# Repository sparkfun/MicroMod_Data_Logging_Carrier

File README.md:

SparkFun MicroMod Data Logging Carrier Board
========================================

[SparkFun MicroMod Data Logging Carrier Board (DEV-16829)](https://www.sparkfun.com/products/16829)

The SparkFun MicroMod Data Logging Carrier Board offers a highly customizable, low-power data logging platform using the MicroMod system allowing you to choose your own Processor Board to pair with the Carrier Board. The board features several connections for data collection including I<sup>2</sup>C, SPI and Serial UART.

Repository Contents
-------------------

* **/Examples** - Arduino example sketches
* **/Hardware** - Eagle design files (.brd, .sch)

Documentation
--------------
* **[Hookup Guide](https://learn.sparkfun.com/tutorials/micromod-data-logging-carrier-board-hookup-guide)** - Basic hookup guide for the SparkFun MicroMod Data Logging Carrier Board
* **[MicroMod Info Page](https://ww.sparkfun.com/micromod)** - MicroMod Information Page

Version History
---------------
* **[DEV-16829](https://www.sparkfun.com/products/16829)** - Initial release.

License Information
-------------------

This product is _**open source**_! 

Please review the LICENSE.md file for license information. 

If you have any questions or concerns on licensing, please contact technical support on our [SparkFun forums](https://forum.sparkfun.com/viewforum.php?f=152).

Distributed as-is; no warranty is given.

- Your friends at SparkFun.

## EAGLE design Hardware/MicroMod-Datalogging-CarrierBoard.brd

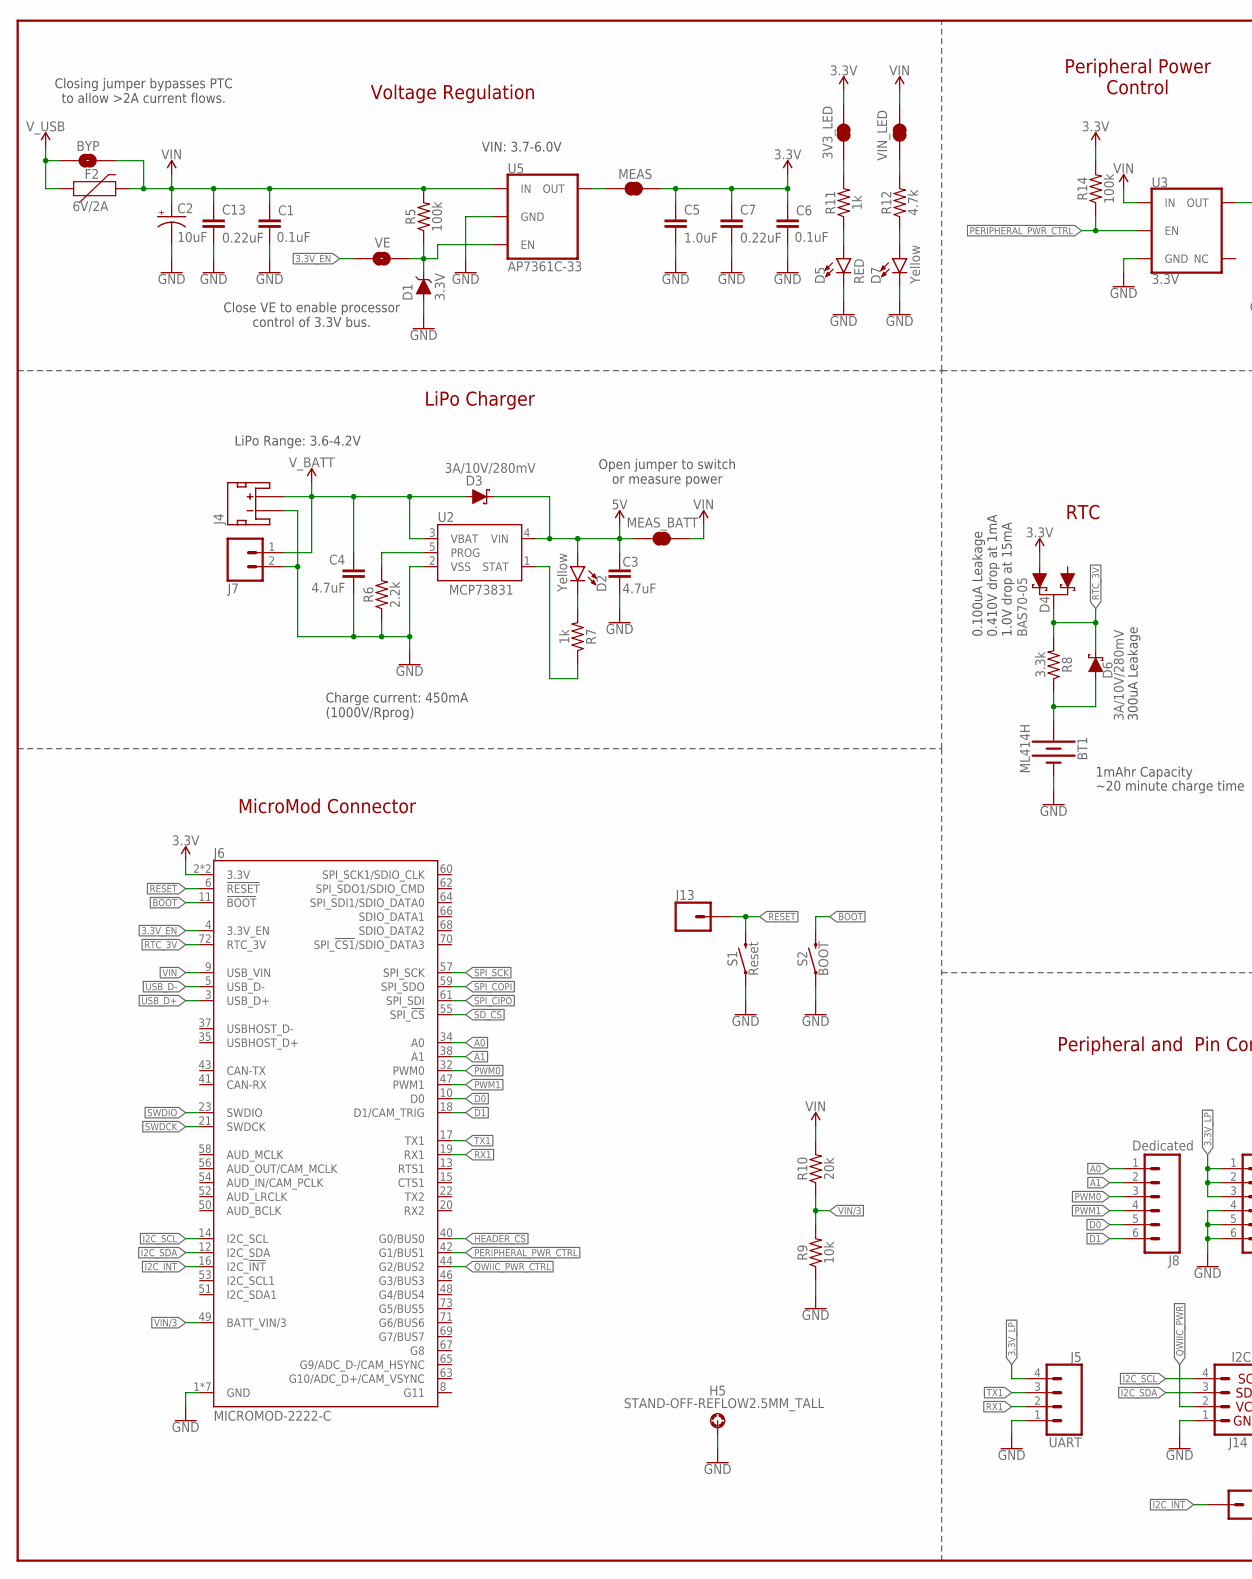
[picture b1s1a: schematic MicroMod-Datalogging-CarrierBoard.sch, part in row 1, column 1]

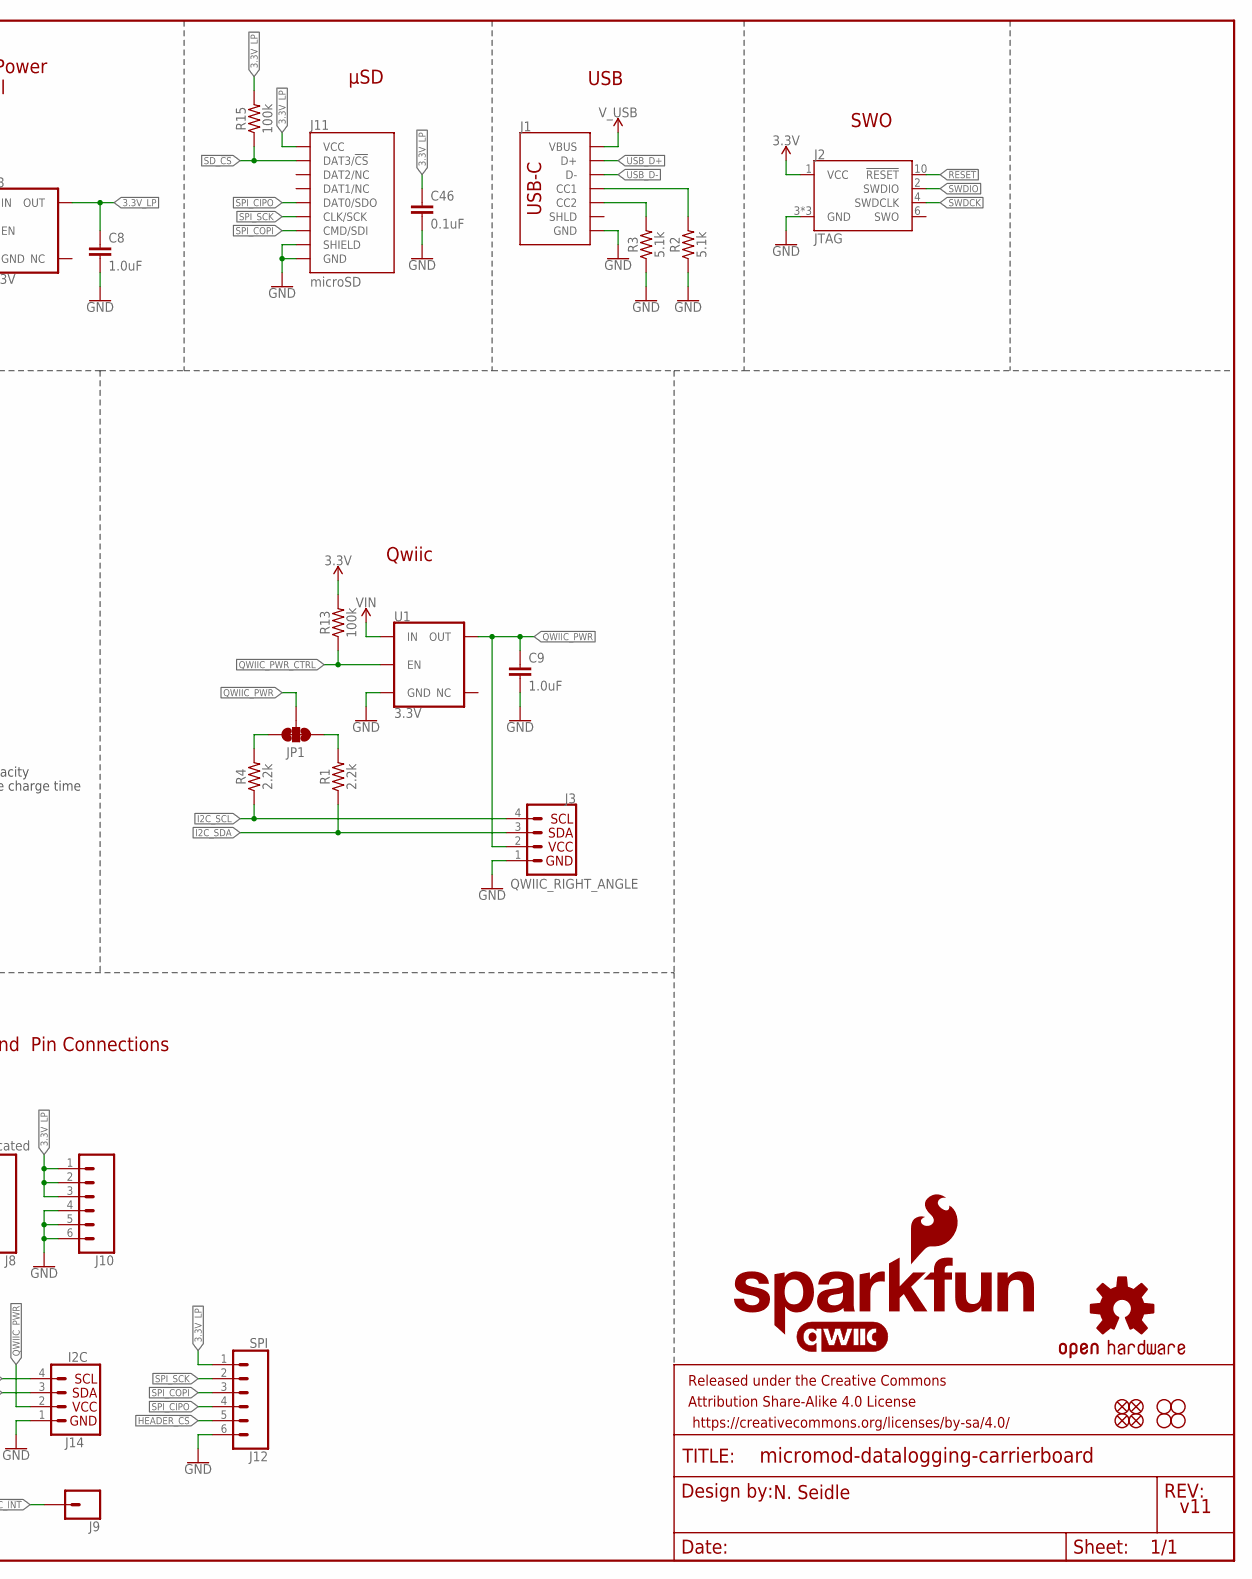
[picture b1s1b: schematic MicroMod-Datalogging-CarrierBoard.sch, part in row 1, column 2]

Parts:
3V3_LED: JUMPER-SMT_2_NC_TRACE_SILK; SMT-JUMPER_2_NC_TRACE_SILK
BT1: ML414H; ML414H_IV01E
BYP: JUMPER-SMT_2_NO_SILK; SMT-JUMPER_2_NO_SILK
C1, C6, C46: 0.1uF; 0603
C2: 10uF; EIA3216
C3, C4: 4.7uF; 0603
C5, C8, C9: 1.0uF; 0603
C7, C13: 0.22uF; 0603
D1: 3.3V; SOD-323
D2, D7: Yellow; LED-0603
D3, D6: 3A/10V/280mV; SOD-323
D4: BAS70-05; SOT23-3
D5: RED; LED-0603
F2: 6V/2A; 1210
FD1, FD2, FD3, FD4: FIDUCIALUFIDUCIAL; FIDUCIAL-MICRO
FRAME1: FRAME-LEDGER; CREATIVE_COMMONS
H1, H2, H3, H4: STAND-OFF
H5: STAND-OFF-REFLOW2.5MM_TALL; STAND-OFF-REFLOW-M2.5
J1: USB_C_2-LAYER_PADS; USB-C-16P-2LAYER-PADS
J2: JTAG; 2X5-PTH-1.27MM
J3: QWIIC_RIGHT_ANGLE; JST04_1MM_RA
J4: JST_2MM_MALE; JST-2-SMD
J5: UART; 1X04_NO_SILK
J6: MICROMOD-2222-C; M.2-CONNECTOR-E
J7: CONN_021X02_NO_SILK; 1X02_NO_SILK
J8: Dedicated; 1X06_NO_SILK
J9, J13: CONN_01PTH_NO_SILK_YES_STOP; 1X01_NO_SILK
J10: CONN_06NO_SILK_NO_POP; 1X06_NO_SILK
J11: microSD; MICRO-SD-SOCKET
J12: SPI; 1X06_NO_SILK
J14: I2C; 1X04_NO_SILK
JP1: JUMPER-SMT_3_2-NC_TRACE_SILK; SMT-JUMPER_3_2-NC_TRACE_SILK
LOGO1: SFE_LOGO_NAME_FLAME.1_INCH; SFE_LOGO_NAME_FLAME_.1
LOGO2: QWIIC_LOGO_CONNECTOR; QWIIC_5.5MM
LOGO3: OSHW-LOGOMINI; OSHW-LOGO-MINI
MEAS: JUMPER-COMBO_2_NC_TRACE; COMBO-JUMPER_2_NC_TRACE
MEAS_BATT: JUMPER-COMBO_2_NC_TRACE; COMBO-JUMPER_2_NC_TRACE
R1, R4, R6: 2.2k; 0603
R2, R3: 5.1k; 0603
R5, R13, R14, R15: 100k; 0603
R7, R11: 1k; 0603
R8: 3.3k; 0603
R9: 10k; 0603
R10: 20k; 0603
R12: 4.7k; 0603
S1: Reset; TACTILE_SWITCH_SMD_5.2MM
S2: BOOT; TACTILE_SWITCH_SMD_5.2MM
U1, U3: 3.3V; SOT23-5
U2: MCP73831; SOT23-5
U5: AP7361C-33; UDFN-8
VE: JUMPER-SMT_2_NO_SILK; SMT-JUMPER_2_NO_SILK
VIN_LED: JUMPER-SMT_2_NC_TRACE_SILK; SMT-JUMPER_2_NC_TRACE_SILK

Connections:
3.3V: 3V3_LED.2, C5.1, C6.1, C7.1, D4.2 (A1), J2.1 (VCC), J6.2 (3.3V), J6.74 (3.3V), MEAS.2, MEAS.4 (2), R13.2, R14.2
3.3V_EN: J6.4 (3.3V_EN), VE.1
3.3V_EN_VE: D1.C, R5.1, U5.5 (EN), VE.2
3.3V_LP: C8.1, C46.1, J5.4, J10.1, J10.2, J10.3, J11.VCC, J12.1, R15.2, U3.5 (OUT)
5V: C3.1, D2.A, D3.C, MEAS_BATT.1, MEAS_BATT.3 (1), U2.4 (VIN)
!BOOT!: J6.11 (!BOOT!), S2.3 (2), S2.4 (2)
!RESET!: J2.10 (!RESET), J6.6 (!RESET!), J13.1, S1.3 (2), S1.4 (2)
A0: J6.34 (A0), J8.1
A1: J6.38 (A1), J8.2
CHG_LED: R7.1, U2.1 (STAT)
D0: J6.10 (D0), J8.5
D1: J6.18 (D1/CAM_TRIG), J8.6
GND: BT1.-, C1.2, C2.-, C3.2, C4.2, C5.2, C6.2, C7.2, C8.2, C9.2, C13.2, C46.2, D1.A, D5.C, D7.C, H5.1, J1.GND, J1.GND2 (GND), J2.3 (GND), J2.5 (GND), J2.9 (GND), J3.1, J4.1 (-), J5.1, J6.1 (GND), J6.7 (GND), J6.33 (GND), J6.36 (GND), J6.39 (GND), J6.45 (GND), J6.75 (GND), J7.2, J10.4, J10.5, J10.6, J11.CD1 (SHIELD), J11.GND, J11.GND1 (GND), J11.GND3 (GND), J12.6, J14.1, R2.1, R3.1, R6.1, R9.1, S1.1, S1.2 (1), S2.1, S2.2 (1), U1.2 (GND), U2.2 (VSS), U3.2 (GND), U5.4 (GND), U5.EP (GND)
HEADER_!CS!: J6.40 (G0/BUS0), J12.5
I2C_!INT!: J6.16 (I2C_!INT!), J9.1
I2C_SCL: J3.4, J6.14 (I2C_SCL), J14.4, R4.1
I2C_SDA: J3.3, J6.12 (I2C_SDA), J14.3, R1.1
unnamed: MEAS.1, MEAS.3 (1), U5.1 (OUT)
unnamed: JP1.3, R4.2
unnamed: JP1.1, R1.2
unnamed: D2.C, R7.2
unnamed: D5.A, R11.1
unnamed: 3V3_LED.1, R11.2
unnamed: R6.2, U2.5 (PROG)
unnamed: R12.2, VIN_LED.1
unnamed: D7.A, R12.1
unnamed: J1.A5 (CC1), R2.2
unnamed: J1.B5 (CC2), R3.2
unnamed: BT1.+, D6.A, R8.1
PERIPHERAL_PWR_CTRL: J6.42 (G1/BUS1), R14.1, U3.3 (EN)
PWM0: J6.32 (PWM0), J8.3
PWM1: J6.47 (PWM1), J8.4
QWIIC_PWR: C9.1, J3.2, J14.2, JP1.2, U1.5 (OUT)
QWIIC_PWR_CTRL: J6.44 (G2/BUS2), R13.1, U1.3 (EN)
RTC_3V: D4.3 (C), D6.C, J6.72 (RTC_3V), R8.2
RX1: J5.2, J6.19 (RX1)
SD_!CS!: J6.55 (SPI_!CS!), J11.CS/DAT3 (DAT3/!CS!), R15.1
SPI_CIPO: J6.61 (SPI_SDI), J11.DO/DAT0 (DAT0/SDO), J12.4
SPI_COPI: J6.59 (SPI_SDO), J11.DI/CMD (CMD/SDI), J12.3
SPI_SCK: J6.57 (SPI_SCK), J11.SCLK (CLK/SCK), J12.2
SWDCK: J2.4 (SWDCLK), J6.21 (SWDCK)
SWDIO: J2.2 (SWDIO), J6.23 (SWDIO)
TX1: J5.3, J6.17 (TX1)
USB_D+: J1.A6 (D+), J1.B6 (D+), J6.3 (USB_D+)
USB_D-: J1.A7 (D-), J1.B7 (D-), J6.5 (USB_D-)
VIN: BYP.2, C1.1, C2.+, C13.1, F2.2, J6.9 (USB_VIN), MEAS_BATT.2, MEAS_BATT.4 (2), R5.2, R10.2, U1.1 (IN), U3.1 (IN), U5.8 (IN), VIN_LED.2
VIN/3: J6.49 (BATT_VIN/3), R9.2, R10.1
V_BATT: C4.1, D3.A, J4.2 (+), J7.1, U2.3 (VBAT)
V_USB: BYP.1, F2.1, J1.VBUS1 (VBUS), J1.VBUS2 (VBUS)

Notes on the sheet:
μSD
300uA Leakage
~20 minute charge time
1mAhr Capacity
SWO
USB
Peripheral and Pin Connections
Qwiic
RTC
Voltage Regulation
MicroMod Connector
LiPo Charger
LiPo Range: 3.6-4.2V
Charge current: 450mA (1000V/Rprog)
Open jumper to switch or measure power
Peripheral Power Control
0.100uA Leakage 0.410V drop at 1mA 1.0V drop at 15mA
Closing jumper bypasses PTC to allow >2A current flows.
VIN: 3.7-6.0V
N. Seidle
v11
Close VE to enable processor control of 3.3V bus.

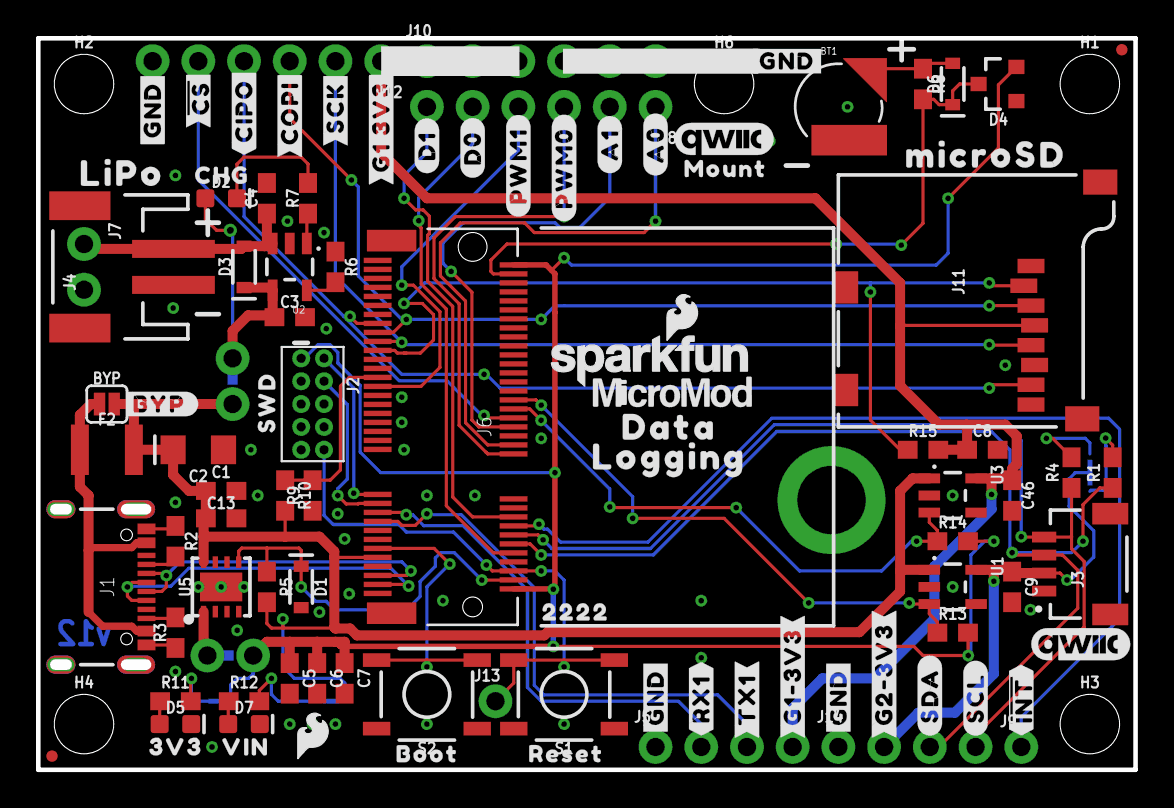
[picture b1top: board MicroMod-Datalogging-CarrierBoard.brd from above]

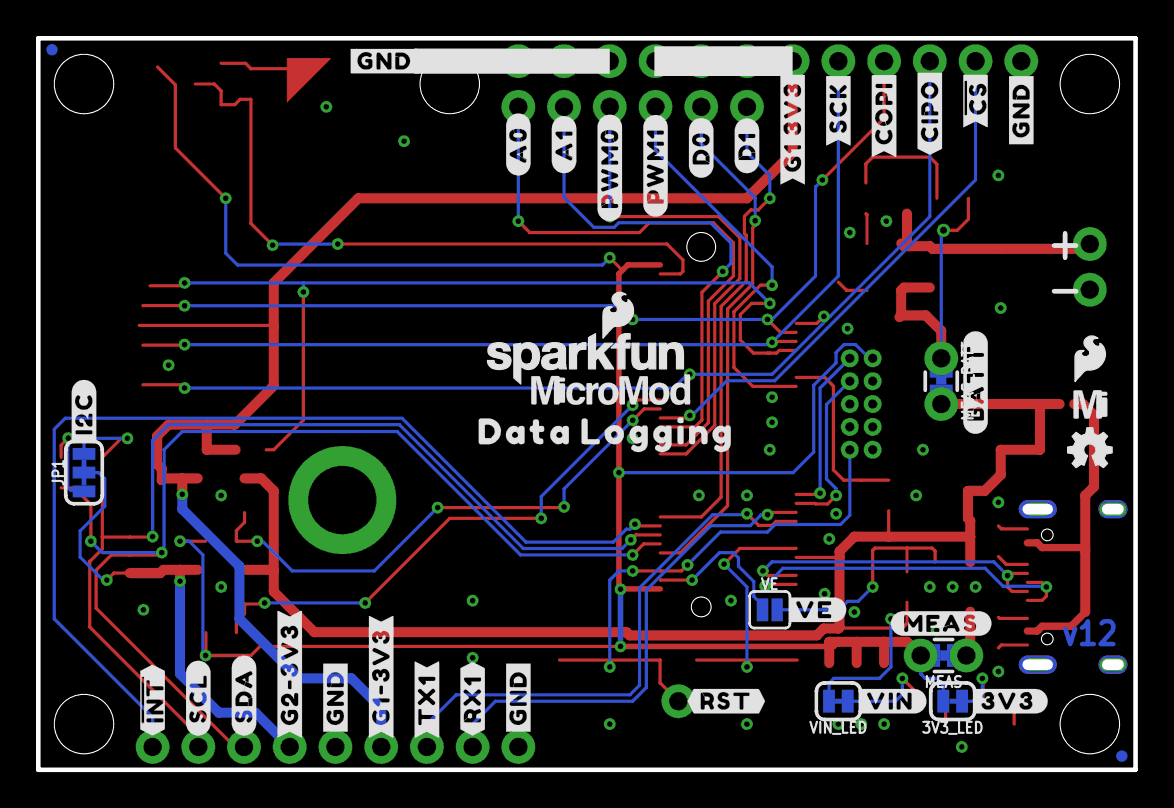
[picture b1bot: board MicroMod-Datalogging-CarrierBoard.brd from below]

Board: 2 copper layers, 60.6 x 40.3 mm, 149 parts (44 on the bottom side), 49 nets.

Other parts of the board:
H6: STAND-OFF
LOGO4: SFE_LOGO_NAME_FLAME.1_INCH; SFE_LOGO_NAME_FLAME_.1
LOGO5: QWIIC_LOGO_CONNECTOR; QWIIC_5.5MM
U$1, U$66: SFE_LOGO_FLAME_.1
U$2, U$76: #D1#0
U$3, U$77: #D0#0
U$4: #3V3#2
U$5: #BATT#0
U$6, U$18, U$24, U$27, U$32, U$34, U$36, U$42: #GND#0
U$7, U$8: #SCK#0
U$9, U$81: #PWM1#1
U$10, U$80: #PWM0#0
U$11: MICROSD0
U$12, U$79: #A1#2
U$13, U$78: #A0#3
U$14: MOUNT0
U$15: LIPO0
U$16, U$23: DATA0
U$17, U$86: #RX1#1
U$19, U$26: LOGGING1
U$20: 22220
U$21, U$89: #TX1#2
U$22: #I2C#0
U$25, U$90: #G1#3V3#0
U$28: #MEAS#3
U$29, U$83: #G2#3V3#3
U$30: #RST#0
U$31, U$88: #SDA#4
U$33: #VIN#1
U$35, U$87: #SCL#5
U$37, U$63: MICROMOD_LOGO_.35
U$38, U$82: ##INT##6
U$39, U$40: #CIPO#0
U$41: #VE#0
U$50, U$51: ##CS##0
U$62: MICROMOD_MI_LOGO_.35
U$64, U$65: #G1_3V3#0
U$72, U$73: #COPI#0
U$91: BOOT0
U$92: RESET1
U$93: 3V30
U$94: VIN1
U$95: #BYP#3
U$96: CHG1
U$97: SWD0

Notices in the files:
parts and their libraries:
SparkFun-Aesthetics: Licensing: Creative Commons ShareAlike 4.0 International - https://creativecommons.org/licenses/by-sa/4.0
SparkFun-Aesthetics: Released under the Creative Commons Attribution Share-Alike 4.0 License
SparkFun-Aesthetics: https://creativecommons.org/licenses/by-sa/4.0
